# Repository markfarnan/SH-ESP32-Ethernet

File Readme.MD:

Ethernet TopHat for the SH-ESP32 board.

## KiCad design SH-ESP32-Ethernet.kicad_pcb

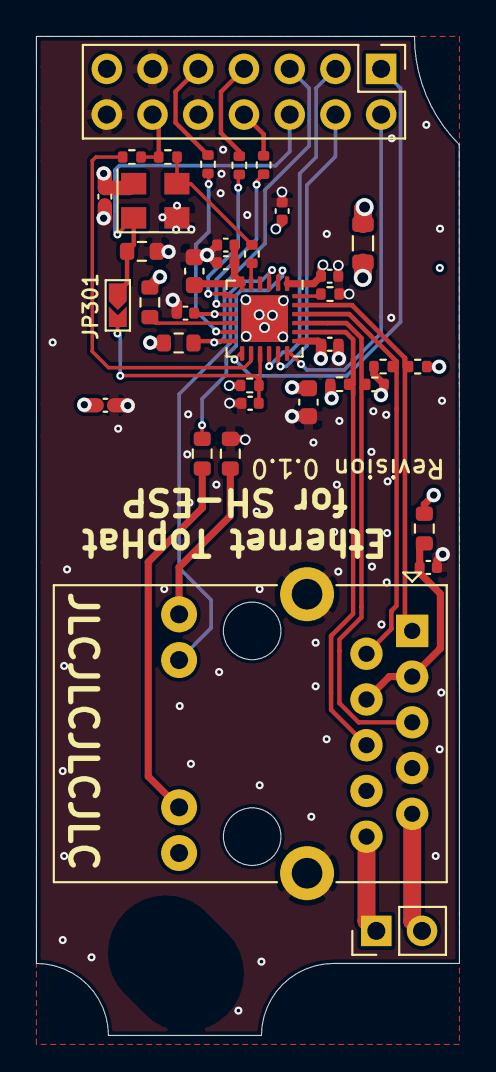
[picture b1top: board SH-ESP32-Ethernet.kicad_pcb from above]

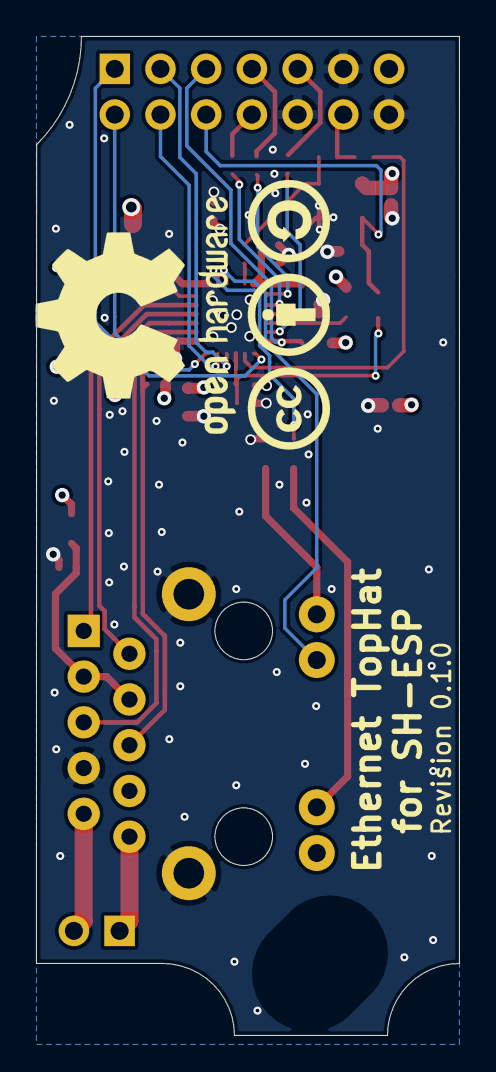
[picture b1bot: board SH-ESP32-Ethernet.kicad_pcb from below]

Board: 4 copper layers, 23.5 x 55.5 mm, 40 parts (2 on the bottom side), 34 nets.

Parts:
C301: 470pf; C_0402_1005Metric
C302, C306: 1uf; C_0402_1005Metric
C303, C304: 4.7uF; C_0603_1608Metric
C305, C307, C1001, C1002, C1003, C1004: 100nF; C_0402_1005Metric
C308: 22nF; C_0402_1005Metric
FB301: GZ2012D601TF; L_0805_2012Metric
H1002: MountingHole; MountingSlot_3.2mm_M3_Unplated
J301: RJ45__HY931147C_MAG_LED_POE; RJ45_HANRUN-HY931147C-Horizontal
J302: GPIO; PinHeader_2x07_P2.54mm_Vertical
J303: Conn_01x03; PinHeader_1x02_P2.54mm_Vertical
JP301: SolderJumper_2_Open; SolderJumper-2_P1.3mm_Open_TrianglePad_Narrow
LOGO_CC: LOGO; cc-by-sa_silkscreen
OSHW: OSHW-Logo2_14.6x12mm_SilkScreen
R301, R302, R303: 1.5k; R_0603_1608Metric
R304, R305, R306, R307, R308, R318: 33R; R_0402_1005Metric
R309: 270; R_0402_1005Metric
R310, R311, R312, R314: 49.9; R_0402_1005Metric
R313: 12.1k; R_0402_1005Metric
R315: 0R; R_0603_1608Metric
R316, R317: 270; R_0603_1608Metric
U301: LAN8720A; QFN-24-1EP_4x4mm_P0.5mm_EP2.6x2.6mm
X301: 50Mhz; Oscillator_SMD_SeikoEpson_SG8002CE-4Pin_3.2x2.5mm

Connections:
+3V3: C1001.2, C1002.2, C1003.2, C1004.2, FB301.2, J302.13, R301.1, R302.1, R309.2, U301.9, X301.4
/IOHeader/CLKIN: R307.1, U301.5
/IOHeader/LED_R_AN: J301.13, R317.1
/IOHeader/LED_Y_AN: J301.11, R316.1
/IOHeader/LED_Y_CA: J301.12, U301.3
/IOHeader/PHY_CLK: J302.12, R308.1, R318.2
/IOHeader/PHY_MDC: J302.1, U301.13
/IOHeader/PHY_MDIO: J302.5, R301.2, U301.12
/IOHeader/PHY_RESET_N: J302.6, JP301.1, R303.1, X301.1
/IOHeader/RMII_EN: J302.3, U301.16
/IOHeader/RMII_RXD0: J302.8, R304.2
/IOHeader/RMII_RXD1: J302.7, R305.2
/IOHeader/RMII_TXD0: J302.4, U301.17
/IOHeader/RMII_TXD1: J302.2, U301.18
/IOHeader/RMI_CRS_DV: J302.9, R306.2
/IOHeader/RX+: J301.1, R312.2, U301.23
/IOHeader/RX-: J301.2, R314.2, U301.22
/IOHeader/TX+: J301.5, R310.2, U301.21
/IOHeader/TX-: J301.6, R311.2, U301.20
/IOHeader/VDDCR: C301.1, C302.1, C303.2, U301.6
/IOHeader/nINTSEL-LED2: R317.2, U301.2
/IOHeader/nRST: C306.1, JP301.2, R309.1, U301.15
GND: C301.2, C302.2, C303.1, C304.1, C305.1, C306.2, C307.1, C308.1, C1001.1, C1002.1, C1003.1, C1004.1, J301.7, J301.15, J302.10, J302.11, J302.14, R303.2, R313.2, R316.2, U301.25, X301.2
unnamed: C308.2, J301.3, J301.4, R315.1
unnamed: J301.9, J303.2
unnamed: J301.10, J303.1
unnamed: R302.2, U301.10
unnamed: R304.1, U301.8
unnamed: R305.1, U301.7
unnamed: R306.1, U301.11
unnamed: R307.2, R308.2, X301.3
unnamed: R313.1, U301.24
unnamed: R318.1, U301.14
VDDA: C304.2, C305.2, C307.2, FB301.1, J301.14, R310.1, R311.1, R312.1, R314.1, R315.2, U301.1, U301.19

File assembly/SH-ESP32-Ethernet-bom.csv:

Comment,Designator,Footprint,LCSC
"100nF","C305,C307,C1001,C1002,C1003,C1004","Capacitor_SMD:C_0402_1005Metric","C1525"
"470pf","C301","Capacitor_SMD:C_0402_1005Metric"," C1537"
"1uf","C302,C306","Capacitor_SMD:C_0402_1005Metric","C52923"
"4.7uF","C303,C304","Capacitor_SMD:C_0603_1608Metric","C19666"
"22nF","C308","Capacitor_SMD:C_0402_1005Metric","C1532"
"GZ2012D601TF","FB301","Inductor_SMD:L_0805_2012Metric","C1017"
"MountingHole","H1002","SH-ESP32:MountingHole_3.2mm_M3_Unplated",""
"RJ45__HY931147C_MAG_LED_POE","J301","SH-ESP32-Ethernet:RJ45_HANRUN-HY931147C-Horizontal","C91754"
"GPIO","J302","Connector_PinHeader_2.54mm:PinHeader_2x07_P2.54mm_Vertical","C358701"
"Conn_01x03","J303","Connector_PinHeader_2.54mm:PinHeader_1x02_P2.54mm_Vertical",""
"SolderJumper_2_Open","JP301","SH-ESP32:SolderJumper-2_P1.3mm_Open_TrianglePad_Narrow",""
"1.5k","R301,R302,R303","Resistor_SMD:R_0603_1608Metric","C22843"
"33R","R304,R305,R306,R307,R308","Resistor_SMD:R_0402_1005Metric","C25105"
"270","R309","Resistor_SMD:R_0402_1005Metric","C25900"
"49.9","R310,R311,R312,R314","Resistor_SMD:R_0402_1005Metric","C25120"
"12.1k","R313","Resistor_SMD:R_0402_1005Metric","C25852"
"0R","R315","Resistor_SMD:R_0603_1608Metric","C21189"
"270","R316,R317","Resistor_SMD:R_0603_1608Metric","C22966"
"LAN8720A","U301","Package_DFN_QFN:QFN-24-1EP_4x4mm_P0.5mm_EP2.6x2.6mm","C45223"
"50Mhz","X301","Oscillator:Oscillator_SMD_SeikoEpson_SG8002CE-4Pin_3.2x2.5mm","C46327"

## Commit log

2020-11-27 Initial Commit - Moved away from SH-ESP32 Repo
2020-11-27 Finalise for Production - LCSC Part numbers - Fix Jack footprint for missing Pad - Sheet names
2020-11-27 Production files for Rev 0.1
2021-01-20 Update for SH-ESP R0.3 Header & Mounting Hole Positions
2021-01-20 Updates for missing resistor / route on Clock line - Created some major re-routing / tidy up

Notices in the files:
SH-ESP32-Ethernet.kicad_pcb:
Sailor Hat for ESP32 is licensed under CC BY-SA 4.0.
